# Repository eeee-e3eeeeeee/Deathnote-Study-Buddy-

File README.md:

# Deathnote-Study-Buddy-
The deathnote study buddy is a study buddy based off of the classic anime Deathnote. It has study timers, and notifies you if you get distracted and move it around. It plays looping gifs, and also when its not being used as a timer it can be used as a clock.

## What it does
- **Live Clock:** Syncs the current time over Wi-Fi.
- **Pomodoro Modes:** Easily switch between 25-minute focus blocks, 5-minute breaks, and heavy 50-minute deep focus sessions.
- **Animated Backgrounds:** Streams looping GIFs.
- **Anti-Cheat Motion Detector:** Uses an LIS3DH accelerometer to monitor movement. If you shake or move the device too much, it flashes an "L IS WATCHING" warning to force you back to work.
- **Simple Controls:** Managed with two push buttons.

## Wiring & Pin Map
| Function | XIAO Pin |
|---|---|
| TFT DIN/MOSI | D10 |
| TFT CLK/SCK | D3 |
| TFT DC | D1 |
| TFT RST | D2 |
| TFT CS | GND *(only if your module supports permanently tied CS)* |
| LIS3DH SDA | D4 |
| LIS3DH SCL | D5 |
| Start/Pause Button | D6 to GND |
| Mode Button | D7 to GND |

## Getting Started (Arduino IDE)
1. Install the Arduino IDE along with the Espressif ESP32 board package.
2. Set your board target to **XIAO ESP32C3**.
3. Open the Library Manager and install these dependencies:
   - Adafruit GFX Library
   - Adafruit ST7735 and ST7789 Library
   - Adafruit LIS3DH
   - Adafruit Unified Sensor
   - AnimatedGIF (by Larry Bank)
5. Open `deathnotestudybuddy_oct11a.ino`, select the correct serial port, and hit upload.

## Adding Animations (`.gif`)
will update this when i get the physical board and can add gifs to it

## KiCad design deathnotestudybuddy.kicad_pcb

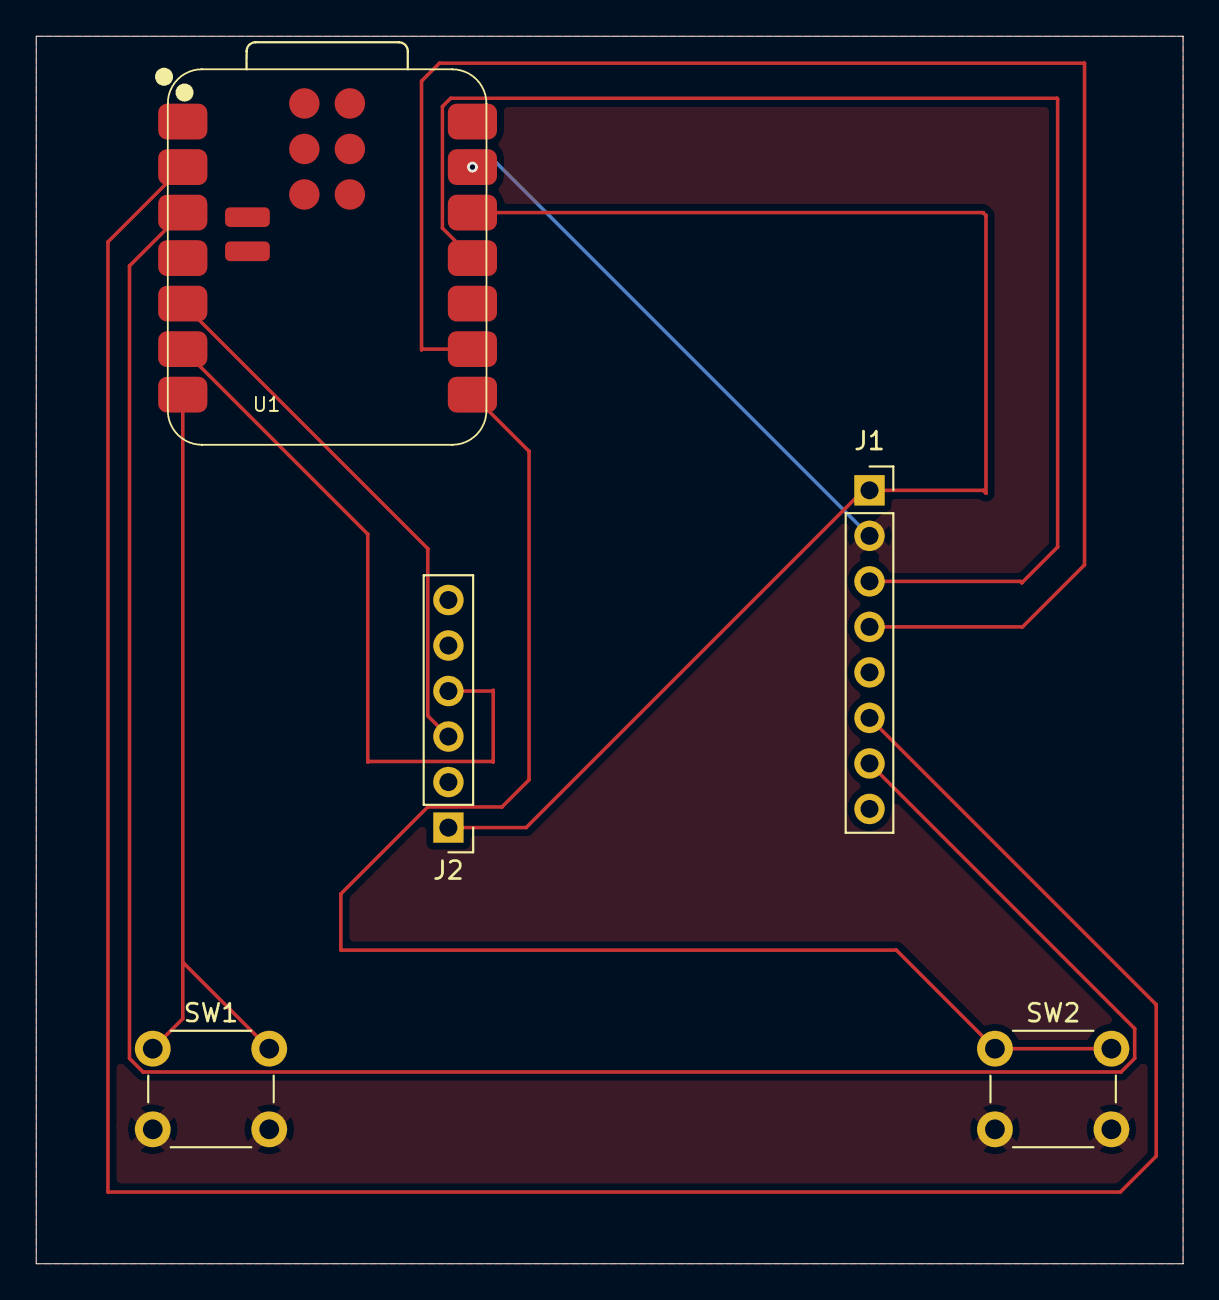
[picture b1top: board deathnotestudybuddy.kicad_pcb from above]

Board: 2 copper layers, 64.0 x 68.5 mm, 5 parts (0 on the bottom side), 10 nets.

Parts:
J1: Conn_01x08; PinSocket_1x08_P2.54mm_Vertical
J2: Conn_01x06; PinHeader_1x06_P2.54mm_Vertical
SW1: A; SW_PUSH_6mm
SW2: B; SW_PUSH_6mm
U1: XIAO-ESP32-C3-SMD

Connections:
+3V3: J1.1, J2.1, U1.12 (3V3_OUT)
/BTN_MODE: SW2.1, U1.8 (D7)
/BTN_START: SW1.1, U1.7 (D6)
/SENSOR_SCL: J2.4, U1.6 (D5)
/SENSOR_SDA: J2.3, U1.5 (D4)
/TFT_CLK: J1.4, U1.9 (D8)
/TFT_DC: J1.6, U1.2 (D1)
/TFT_MOSI: J1.3, U1.11 (D10)
/TFT_RST: J1.7, U1.3 (D2)
GND: J1.2, J2.2, SW1.2, SW2.2, U1.13 (GND)

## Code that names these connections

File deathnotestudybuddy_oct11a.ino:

void setup() {
  // put your setup code here, to run once:

}

void loop() {
  
constexpr int TFT_CS = -1;       
constexpr int TFT_RST = D2;
constexpr int TFT_SCK = D3;
constexpr int TFT_MOSI = D10;
constexpr int BTN_START = D6;   
constexpr int BTN_MODE = D7;     
constexpr int I2C_SDA = D4;
constexpr int I2C_SCL = D5;

Adafruit_ST7789 tft(TFT_CS, TFT_DC, TFT_RST);
Adafruit_LIS3DH lis;
AnimatedGIF gif;
File gifFile;
bool sensorOK = false, fsOK = false, gifIsOpen = false;
bool timerRunning = false, timerDone = false, motionScreen = false;
uint8_t mode = 0;
const uint16_t minutesByMode[] = {25, 5, 50};
const char *modeLabel[] = {"FOCUS 25", "BREAK 5", "DEEP FOCUS 50"};
uint32_t remainingMs = 25UL * 60 * 1000;
uint32_t lastTick = 0, lastDraw = 0, motionUntil = 0, lastMotion = 0;
uint32_t timerStarted = 0;
bool lastStart = HIGH, lastMode = HIGH;
uint32_t startChanged = 0, modeChanged = 0;
float oldX = 0, oldY = 0, oldZ = 9.8;

void centerText(const String &s, int y, uint16_t color, uint8_t size=2) {
  tft.setTextSize(size); tft.setTextColor(color, ST77XX_BLACK);
  int16_t x1,y1; uint16_t w,h;
  tft.getTextBounds(s,0,y,&x1,&y1,&w,&h);
  tft.setCursor((tft.width()-(int)w)/2,y); tft.print(s);
}
void header(const char *s) {
  tft.fillScreen(ST77XX_BLACK);
  centerText(s, 8, ST77XX_RED, 2);
  tft.drawFastHLine(8, 31, tft.width()-16, ST77XX_RED);
}
String timeLeft() {
  uint32_t sec=(remainingMs+999)/1000; char b[12];
  snprintf(b,sizeof(b),"%02lu:%02lu",(unsigned long)(sec/60),(unsigned long)(sec%60));
  return String(b);
}
void drawClock() {
  header("DEATH NOTE");
  struct tm ti;
  if (getLocalTime(&ti, 50)) {
    char tb[20], db[24];
    strftime(tb,sizeof(tb),"%I:%M:%S %p",&ti);
    strftime(db,sizeof(db),"%a, %b %d",&ti);
    centerText(tb,75,ST77XX_WHITE,3); centerText(db,120,ST77XX_CYAN,2);
  } else {
    centerText("CONNECTING WIFI",85,ST77XX_WHITE,1);
    centerText("Clock needs NTP sync",110,ST77XX_CYAN,1);
  }
  centerText("D6: START TIMER",190,ST77XX_WHITE,2);
  centerText("D7: CHANGE MODE",220,ST77XX_YELLOW,1);
}
void drawTimer() {
  header(modeLabel[mode]);
  centerText(timerDone ? "TIME IS UP" : (timerRunning ? "STAY FOCUSED" : "READY?"),
             55, timerDone ? ST77XX_RED : ST77XX_WHITE, 2);
  centerText(timeLeft(),100,ST77XX_CYAN,4);
  centerText(timerRunning ? "D6: PAUSE" : "D6: START",175,ST77XX_WHITE,2);
  centerText("D7: CHANGE MODE",210,ST77XX_YELLOW,1);
  centerText("L IS WATCHING",240,ST77XX_RED,1);
}
void closeGif() {
  if (gifIsOpen) { gif.close(); gifIsOpen=false; }
  if (gifFile) gifFile.close();
}
void *gifOpen(const char *name, int32_t *size) {
  gifFile=LittleFS.open(name,"r");
  if (!gifFile) return nullptr;
  *size=gifFile.size(); return &gifFile;
}
void gifClose(void *handle) {
  File *f=(File*)handle; if (f && *f) f->close();
}
int32_t gifRead(GIFFILE *f, uint8_t *buf, int32_t len) {
  File *file=(File*)f->fHandle; if (!file) return 0;
  int32_t avail=(int32_t)(file->size()-file->position());
  if (len>avail) len=avail; if (len<=0) return 0;
  return file->read(buf,len);
}
int32_t gifSeek(GIFFILE *f, int32_t pos) {
  File *file=(File*)f->fHandle; if (!file) return 0;
  file->seek(pos); return pos;
}
void gifDraw(GIFDRAW *d) {
  
  int y=d->iY+d->y, x=d->iX;
  if (y<0 || y>=tft.height()) return;
  uint8_t *px=d->pPixels; uint16_t *pal=d->pPalette;
  for (int i=0;i<d->iWidth;i++) {
    int xx=x+i; if (xx<0 || xx>=tft.width()) continue;
    if (d->ucHasTransparency && px[i]==d->ucTransparent) continue;
    tft.drawPixel(xx,y,pal[px[i]]);
  }
}
bool openGif(const char *path) {
  if (!fsOK) return false;
  closeGif();
  if (!gif.open(path,gifOpen,gifClose,gifRead,gifSeek,gifDraw)) return false;
  gifIsOpen=true; return true;
}
void startPause() {
  if (timerRunning) {
    uint32_t elapsed=millis()-timerStarted;
    remainingMs = elapsed >= remainingMs ? 0 : remainingMs-elapsed;
    timerRunning=false;
  } else {
    if (timerDone || remainingMs==0) {
      remainingMs=(uint32_t)minutesByMode[mode]*60000UL; timerDone=false;
    }
    timerRunning=true; timerStarted=millis();
    openGif("/gifs/focus.gif");
  }
  drawTimer();
}
void nextMode() {
  mode=(mode+1)%3; timerRunning=false; timerDone=false;
  remainingMs=(uint32_t)minutesByMode[mode]*60000UL;
  closeGif(); drawTimer();
}
void button(int pin, bool &last, uint32_t &changed, void (*action)()) {
  bool now=digitalRead(pin);
  if (now!=last) { last=now; changed=millis(); }
  static bool startStable=HIGH, modeStable=HIGH;
  bool &stable=(pin==BTN_START)?startStable:modeStable;
  if (millis()-changed>30 && now!=stable) {
    stable=now; if (stable==LOW) action();
  }
}
void motionReaction() {
  motionScreen=true; motionUntil=millis()+5000;
  closeGif(); tft.fillScreen(ST77XX_BLACK);
  centerText("L IS WATCHING",60,ST77XX_RED,2);
  centerText("YOU MOVED.",105,ST77XX_WHITE,2);
  centerText("BACK TO WORK",150,ST77XX_CYAN,2);
  openGif("/gifs/motion.gif");
}
void checkMotion() {
  if (!sensorOK || millis()-lastMotion<120 || motionScreen) return;
  lastMotion=millis(); sensors_event_t e; lis.getEvent(&e);
  float delta=fabs(e.acceleration.x-oldX)+fabs(e.acceleration.y-oldY)+fabs(e.acceleration.z-oldZ);
  oldX=e.acceleration.x; oldY=e.acceleration.y; oldZ=e.acceleration.z;
  if (delta>5.0) motionReaction();
}
void setup() {
  Serial.begin(115200);
  pinMode(BTN_START,INPUT_PULLUP); pinMode(BTN_MODE,INPUT_PULLUP);
  SPI.begin(TFT_SCK,-1,TFT_MOSI,TFT_CS);
  tft.init(240,280); tft.setRotation(0); tft.fillScreen(ST77XX_BLACK);
  Wire.begin(I2C_SDA,I2C_SCL);
  sensorOK=lis.begin(0x18); if (!sensorOK) sensorOK=lis.begin(0x19);
  if (sensorOK) lis.setRange(LIS3DH_RANGE_4_G);
  fsOK=LittleFS.begin(true); if (fsOK) gif.begin(BIG_ENDIAN_PIXELS);
  WiFi.mode(WIFI_STA); WiFi.begin(WIFI_SSID,WIFI_PASSWORD);
  header("DEATH NOTE"); centerText("BOOTING...",100,ST77XX_WHITE,2);
  uint32_t started=millis();
  while (WiFi.status()!=WL_CONNECTED && millis()-started<12000) delay(100);
  if (WiFi.status()==WL_CONNECTED) configTzTime(TIMEZONE,"pool.ntp.org","time.nist.gov");
  drawClock();
}
void loop() {
  button(BTN_START,lastStart,startChanged,startPause);
  button(BTN_MODE,lastMode,modeChanged,nextMode);
  checkMotion();
  if (timerRunning && millis()-lastTick>=250) {
    uint32_t now=millis(), elapsed=now-timerStarted; timerStarted=now; lastTick=now;
    if (elapsed>=remainingMs) { remainingMs=0; timerRunning=false; timerDone=true; closeGif(); drawTimer(); }
    else remainingMs-=elapsed;
  }
  if (motionScreen && (int32_t)(millis()-motionUntil)>=0) {
    motionScreen=false; closeGif(); if (timerRunning || timerDone) drawTimer(); else drawClock();
  }
  if (gifIsOpen) {
    int delayMs=0;
    if (gif.playFrame(true,&delayMs,nullptr)==0) {
      
      closeGif();
      if (motionScreen) openGif("/gifs/motion.gif");
      else if (timerRunning) openGif("/gifs/focus.gif");
    }
  }
  if (!motionScreen && !gifIsOpen && millis()-lastDraw>=1000) {
    lastDraw=millis(); if (timerRunning || timerDone) drawTimer(); else drawClock();
  }
}


}
